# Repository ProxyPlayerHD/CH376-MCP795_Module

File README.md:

# RTC-USB_Module
This Module combines the CH376S USB/SD Flash Storage Controller with built-in support for the FAT32 file system, and the MCP795XXX Real Time Clock, in a compact and convienent form factor.

This allows for both File IO and Time keeping using a single module and SPI interface.
#

this project includes all the necessary KiCad files, and even pre-exported Gerbers so anyone can order their own boards from a PCB manufacturer like JLCPCB or PCBWay for example.

A Schematic of the board is included in PDF form, but the connector pinouts are listed below for convenience.

## Main Connector (J2) Pinout:

| Pin | Direction |  Name  | Description |
|-----|-----------|--------|-------------|
|  1  | In        | 5V     | 5V Power |
|  2  | In        | GND    | Ground |
|  3  | In        | SCK    | Clock (SPI) |
|  4  | Out       | ~ACT   | CH376S "Active" signal |
|  5  | In        | MOSI   | Data Input (SPI) |
|  6  | Out       | ~IRQ0  | CH376S Interrupt |
|  7  | Out       | MISO   | Data Output (SPI) |
|  8  | Out       | ~IRQ1  | MCP795 Interrupt |
|  9  | In        | ~SS0   | CH376S Select (SPI) |
|  10 | Out       | ~IRQ2  | MCP795 Watch Dog Interrupt |
|  11 | In        | ~SS1   | MCP795 Select (SPI) |
|  12 | Out       | CLKOUT | MCP795 Programmable Clock Output |

## SD Card Connector (J0) Pinout:

| Pin | Direction |  Name  | Description |
|-----|-----------|--------|-------------|
|  1  | Out       | ~SS    | SD Card Select (SPI) |
|  2  | Out       | SCK    | Clock (SPI) |
|  3  | Out       | MOSI   | Data Output (SPI) |
|  4  | In        | MISO   | Data Input (SPI) |
|  5  | Out       | 5V     | 5V Power |
|  6  | Out       | GND    | Ground |

Note that the J0 pinout is the same as for the common Arduino SD Card Modules. as the intend was to allow people to simply plug one of those in instead of having to make their own SD board/adpater.

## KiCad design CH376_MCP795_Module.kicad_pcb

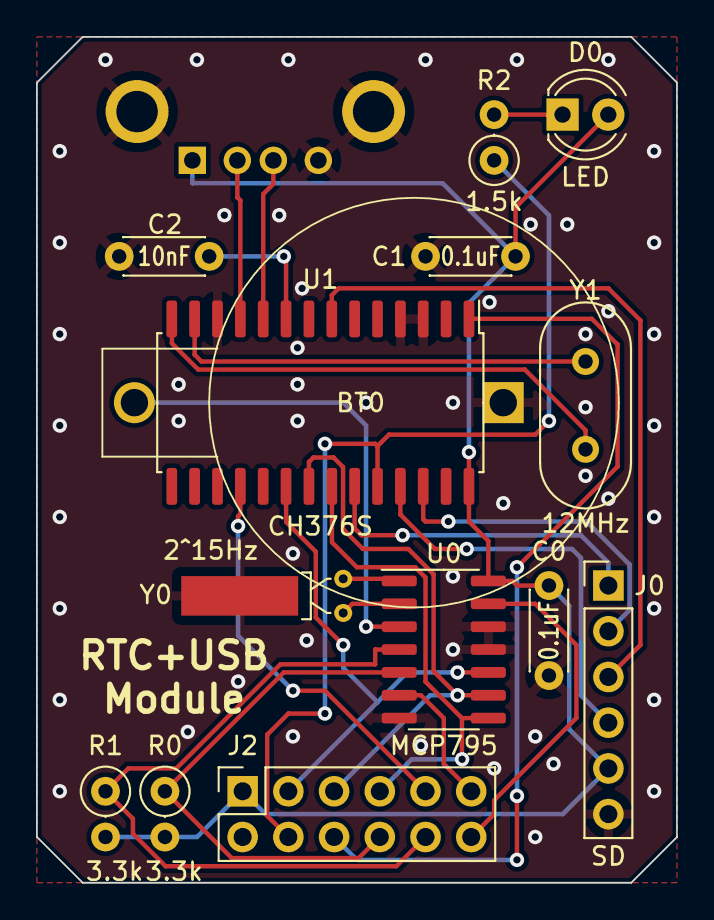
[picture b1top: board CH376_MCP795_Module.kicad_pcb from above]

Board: 2 copper layers, 35.6 x 47.0 mm, 15 parts (1 on the bottom side), 25 nets.

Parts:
BT0: CR2032
C0, C1: 0.1uF; C_Disc_D4.3mm_W1.9mm_P5.00mm
C2: 10nF; C_Disc_D4.3mm_W1.9mm_P5.00mm
D0: LED; LED_D4.0mm
J0: SD; PinHeader_1x06_P2.54mm_Vertical
J1: USB_A; USB_A_CONNFLY_DS1095-WNR0
J2: MAIN; PinSocket_2x06_P2.54mm_Vertical
R0, R1: 3.3k; R_Axial_DIN0207_L6.3mm_D2.5mm_P2.54mm_Vertical
R2: 1.5k; R_Axial_DIN0207_L6.3mm_D2.5mm_P2.54mm_Vertical
U0: MCP795; SOIC-14_3.9x8.7mm_P1.27mm
U1: CH376S; SOIC-28W_7.5x17.9mm_P1.27mm
Y0: 2^15Hz; Crystal_C26-LF_D2.1mm_L6.5mm_Horizontal_1EP_style1
Y1: 12MHz; Crystal_HC49-4H_Vertical

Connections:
/3V3: C2.2, U1.9 (3V3)
/5V: C0.2, C1.2, D0.2 (A), J0.5, J1.1 (VBUS), J2.1, R0.2, R1.2, U0.14 (Vcc), U1.28 (Vcc)
/CLKOUT: J2.12, U0.13 (CLKOUT)
/GND: BT0.1 (GND), C0.1, C1.1, C2.1, J0.6, J1.4 (GND), J1.5 (Shield), J2.2, U0.7 (~GND), U0.11 (EVLS), U0.12 (EVHS), U1.3 (~WR), U1.4 (~RD), U1.12 (GND), Y0.3
/MISO: J2.7, U0.8 (MISO), U1.22 (D7)
/MOSI: J2.5, U0.9 (MOSI), U1.21 (D6)
/SCK: J2.3, U0.10 (SCK), U1.20 (D5)
/SD_MISO: J0.4, U1.25 (SD_MISO)
/SD_MOSI: J0.3, U1.7 (SD_MOSI)
/SD_SCK: J0.2, U1.26 (SD_SCK)
/VBAT: BT0.2 (+3V3), U0.3 (VBAT)
/~ACT: J2.4, R2.1, U1.24 (~ACT)
/~IRQ0: J2.6, U1.1 (~INT)
/~IRQ1: J2.8, R0.1, U0.5 (~IRQ)
/~IRQ2: J2.10, R1.1, U0.4 (~WDO)
/~SD_SS: J0.1, U1.23 (SD_CS)
/~SS0: J2.9, U1.18 (D3)
/~SS1: J2.11, U0.6 (~CS)
unnamed: D0.1 (K), R2.2
unnamed: J1.2 (D-), U1.11 (USB_DM)
unnamed: J1.3 (D+), U1.10 (USB_DP)
unnamed: U0.1 (X1), Y0.1
unnamed: U0.2 (X2), Y0.2
unnamed: U1.14 (XO), Y1.1
unnamed: U1.13 (XI), Y1.2
